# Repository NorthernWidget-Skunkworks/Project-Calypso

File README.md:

# Project-Calypso
The hardware and software designs for a turbidity measurement system, based on the work of a 2018 UMN senior design team

## Project Summary

Our team developed an open-source sensor to measure water turbidity. Turbidity, or "murkiness", increases when the water carries more sediment. Dissolved compounds can also increase turbidity by reducing water clarity. In general, less suspended and dissolved material makes better drinking water. Anyone may download and build this sensor (Design: https://doi.org/10.5281/zenodo.8177929).

*Two LEDs, red and infrared, send beams across the water to be measured, which lies within a transparent tube. These LED beams interact with the water, which reduces transmission and increases sidewas scatter. The detectors record both changes.*

The sensor, called "Project Calypso", shines lights from two LEDs through the water. These LEDs lie at right angles from each other along a clear square plastic tube. Detectors record the LEDs' brightness. The sensor directly across from each LED records light transmission. The sensor at 90 degrees from each LED records light scattering. Sediment in the water blocks the light and reduces transmission. Light can reflect off of sediment and scatter onto the sensor at 90 degrees. The scattering pattern depends on the wavelength of the light and sediment size. Therefore, we use both visible (red) and infrared light to learn about sediment size. Dissolved material reduces light transmission but does not scatter the light sideways. Because of this, Project Calypso can differentiate between sediment and dissolved compounds.

*CAD drawing of the LED and detector mount. Sensors and mount surround a transparent plastic tube with a square cross section. Water, along with any suspended and/or dissolved matter that it carries, fills this tube.*

*3-D printed LED and detctor mount, along with one of the installed custom circuit boards to hold the LEDs and light detectors.*

We characterized the Calypso sensor using standards of known turbidity. Sensor response varied systematically with water cloudiness and light wavelength. The Calypso turbidity-sensor system is not only an open-source alternative. It also provides more information than standard turbidity sensors.

*Increasing concentrations of Formaizin (left to right) cause the water to become systematically cloudier. We characterized the sensor using these standards.*

## Funding Support

Funding for this work came from the ***University of Minnesota Water Resources Center***, with support from the **USGS WRRI** program. This funding supported a grant to Wickert, Sandell, and Karwan, for their proposal entitled, *Open-Source Turbidity Sensor to Monitor Suspended and Dissolved Matter in Surface Water*.

<br/>
<br />This work is licensed under a <a rel="license" href="http://creativecommons.org/licenses/by-sa/4.0/">Creative Commons Attribution-ShareAlike 4.0 International License</a>.

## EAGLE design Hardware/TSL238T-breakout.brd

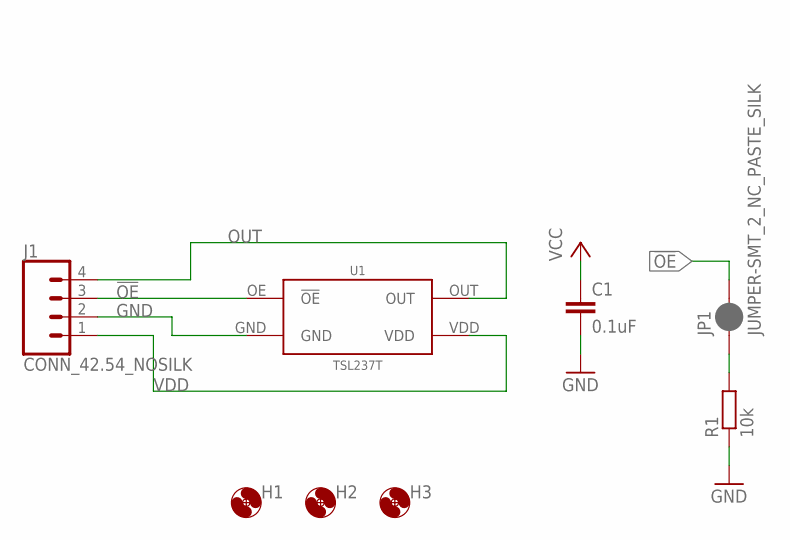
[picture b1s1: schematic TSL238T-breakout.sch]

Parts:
C1: 0.1uF; C0402
H1, H2, H3: MOUNTING_HOLE2_NP; 2_56
J1: CONN_42.54_NOSILK; 1X04_NOSILK
JP1: JUMPER-SMT_2_NC_PASTE_SILK; SMT-JUMPER_2_NC_PASTE_SILK
R1: 10k; R0402
U1: TSL237T

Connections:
!OE: J1.3, JP1.2, U1.OE (!OE)
GND: C1.2, J1.2, R1.1, U1.GND
unnamed: JP1.1, R1.2
OUT: J1.4, U1.OUT
VDD: C1.1, J1.1, U1.VDD

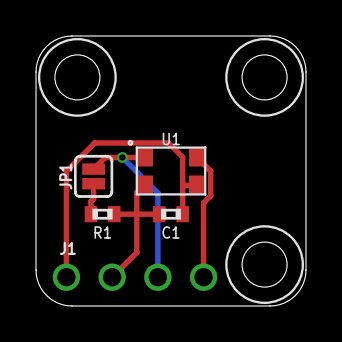
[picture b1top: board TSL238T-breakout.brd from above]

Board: 2 copper layers, 15.0 x 15.0 mm, 8 parts (0 on the bottom side), 5 nets.

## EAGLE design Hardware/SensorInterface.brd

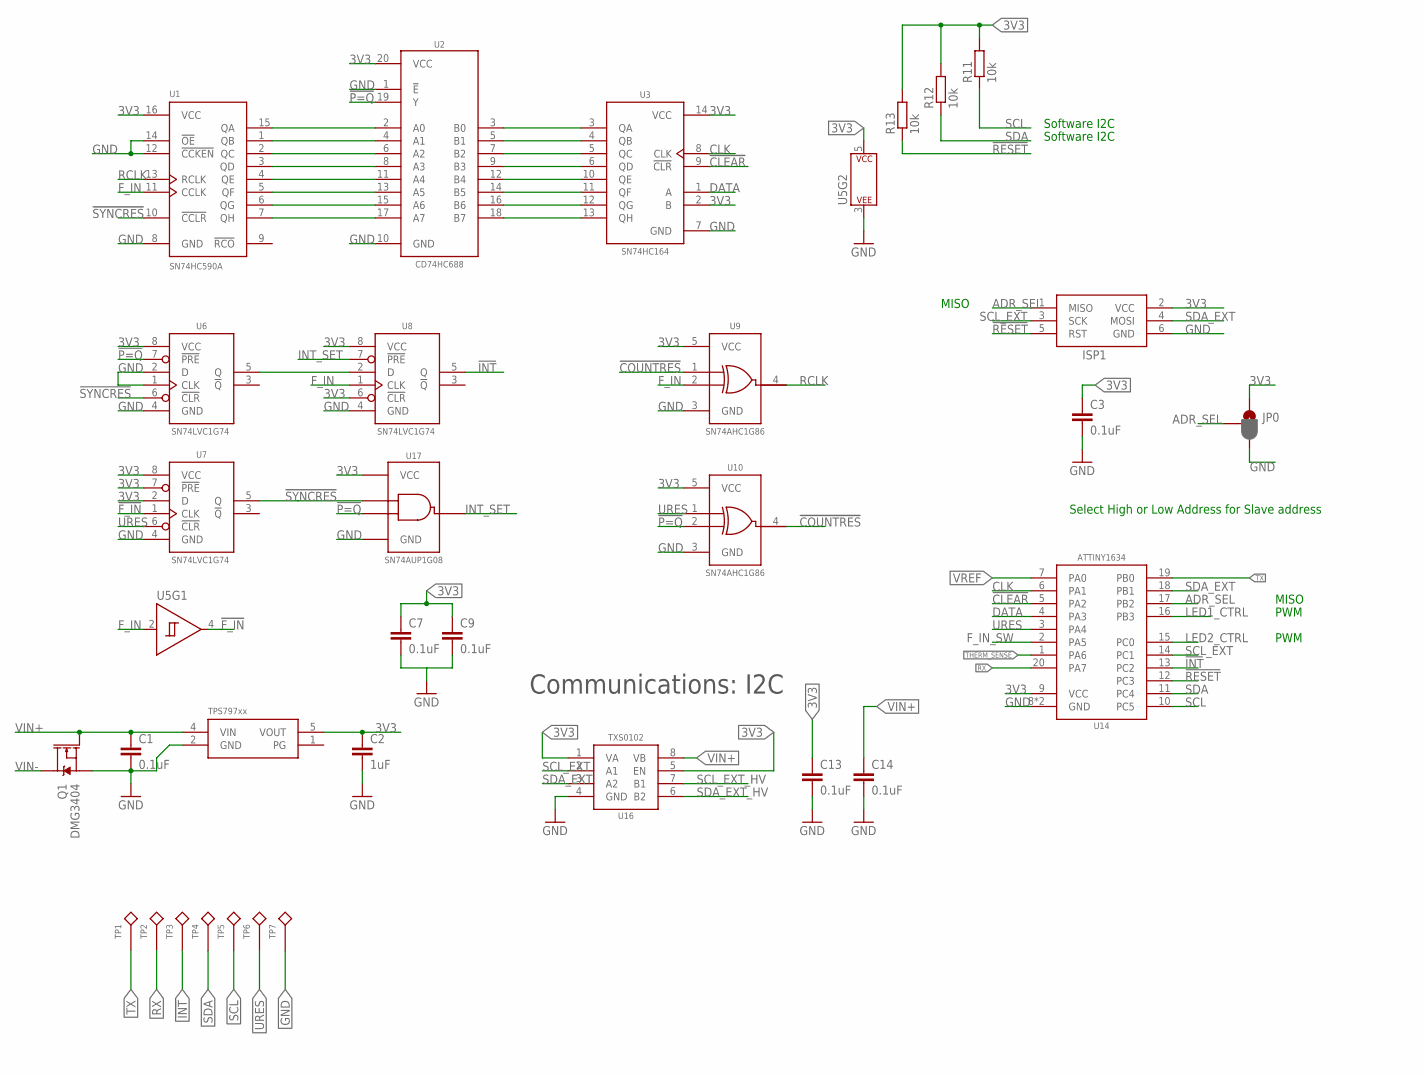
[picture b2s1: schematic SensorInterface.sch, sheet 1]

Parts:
C1, C7, C9: 0.1uF; C0603
C2: 1uF; C0603
C3, C13, C14: 0.1uF; C0402
ISP1: AVRISP-6; AVRISP
JP0: JUMPER-SMT_3_1-NC_PASTE_SILK; SMT-JUMPER_3_1-NC_PASTE_SILK
Q1: DMG3404; SOT23-3
R11, R12, R13: 10k; R0402
TP1, TP2, TP3, TP4, TP5, TP6, TP7: TESTPOINTRCU; TESTPOINT_0603
U1: SN74HC590AD; SO16
U2: CD74HCT688DW; SO-20DW
U3: SN74HC164D; SO14
U5: SN74LVC1G14DCK; DCK_R-PDSO-G5
U6, U7, U8: SN74LVC1G74DCU; DCU_(R-PDSO-G8)
U9, U10: SN74AHC1G86DCK; DCK_R-PDSO-G5
U14: ATTINY1634QFN; QFN20
U16: TXS0102DQM; DQM_R-PX2SON-N8
U17: SN74AUP1G08DCK; DCK_R-PDSO-G5
U$1: TPS79733; DCK_R-PDSO-G5

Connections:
3V3: C2.1, C3.1, C7.1, C9.1, C13.1, ISP1.2 (VCC), JP0.1, R11.2, R12.2, R13.2, U1.16 (VCC), U2.20 (VCC), U3.2 (B), U3.14 (VCC), U5.5 (P$V+), U6.8 (VCC), U7.2 (D), U7.7 (!PRE), U7.8 (VCC), U8.6 (!CLR), U8.8 (VCC), U9.5 (VCC), U10.5 (VCC), U14.9 (VCC), U16.1 (VA), U16.5 (EN), U17.5 (VCC), U$1.5 (VOUT); also elsewhere on the board
!CLEAR: U3.9 (!CLR), U14.5 (PA2)
!COUNTRES: U9.1 (A), U10.4 (Y)
!F_IN: U5.4 (Y), U7.1 (CLK)
!INT: TP3.1, U8.5 (Q), U14.13 (PC2)
!P=Q: U2.19 (Y), U6.7 (!PRE), U10.2 (B), U17.2 (B)
!RESET: ISP1.5 (RST), R13.1, U14.12 (PC3)
!SYNCRES: U1.10 (!CCLR), U6.6 (!CLR), U7.5 (Q), U17.1 (A)
ADR_SEL: ISP1.1 (MISO), JP0.2, U14.17 (PB2)
CLK: U3.8 (CLK), U14.6 (PA1)
DATA: U3.1 (A), U14.4 (PA3)
F_IN: U1.11 (CCLK), U5.2 (A), U8.1 (CLK), U9.2 (B); also elsewhere on the board
F_IN_SW: U14.2 (PA5); also elsewhere on the board
GND: C1.2, C2.2, C3.2, C7.2, C9.2, C13.2, C14.2, ISP1.6 (GND), JP0.3, Q1.2 (S), TP7.1, U1.8 (GND), U1.12 (!CCKEN), U1.14 (!OE), U2.1 (!E), U2.10 (GND), U3.7 (GND), U5.3 (P$V-), U6.1 (CLK), U6.2 (D), U6.4 (GND), U7.4 (GND), U8.4 (GND), U9.3 (GND), U10.3 (GND), U14.8 (GND), U14.EP (GND), U16.4 (GND), U17.3 (GND), U$1.2 (GND); also elsewhere on the board
INT_SET: U8.7 (!PRE), U17.4 (Y)
LED1_CTRL: U14.16 (PB3); also elsewhere on the board
LED2_CTRL: U14.15 (PC0); also elsewhere on the board
unnamed: U1.15 (QA), U2.2 (A0)
unnamed: U1.1 (QB), U2.4 (A1)
unnamed: U1.2 (QC), U2.6 (A2)
unnamed: U1.3 (QD), U2.8 (A3)
unnamed: U1.4 (QE), U2.11 (A4)
unnamed: U1.5 (QF), U2.13 (A5)
unnamed: U1.6 (QG), U2.15 (A6)
unnamed: U1.7 (QH), U2.17 (A7)
unnamed: U2.3 (B0), U3.3 (QA)
unnamed: U2.5 (B1), U3.4 (QB)
unnamed: U2.7 (B2), U3.5 (QC)
unnamed: U2.9 (B3), U3.6 (QD)
unnamed: U2.12 (B4), U3.10 (QE)
unnamed: U2.14 (B5), U3.11 (QF)
unnamed: U2.16 (B6), U3.12 (QG)
unnamed: U2.18 (B7), U3.13 (QH)
unnamed: U6.5 (Q), U8.2 (D)
RCLK: U1.13 (RCLK), U9.4 (Y)
RX: TP2.1, U14.20 (PA7)
SCL: R11.1, TP5.1, U14.10 (PC5); also elsewhere on the board
SCL_EXT: ISP1.3 (SCK), U14.14 (PC1), U16.2 (A1)
SCL_EXT_HV: U16.7 (B1); also elsewhere on the board
SDA: R12.1, TP4.1, U14.11 (PC4); also elsewhere on the board
SDA_EXT: ISP1.4 (MOSI), U14.18 (PB1), U16.3 (A2)
SDA_EXT_HV: U16.6 (B2); also elsewhere on the board
THERM_SENSE: U14.1 (PA6); also elsewhere on the board
TX: TP1.1, U14.19 (PB0)
URES: TP6.1, U7.6 (!CLR), U10.1 (A), U14.3 (PA4)
VIN+: C1.1, C14.1, Q1.1 (G), U16.8 (VB), U$1.4 (VIN); also elsewhere on the board
VIN-: Q1.3 (D); also elsewhere on the board
VREF: U14.7 (PA0); also elsewhere on the board

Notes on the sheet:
Software I2C
Select High or Low Address for Slave address
Communications: I2C
PWM
MISO

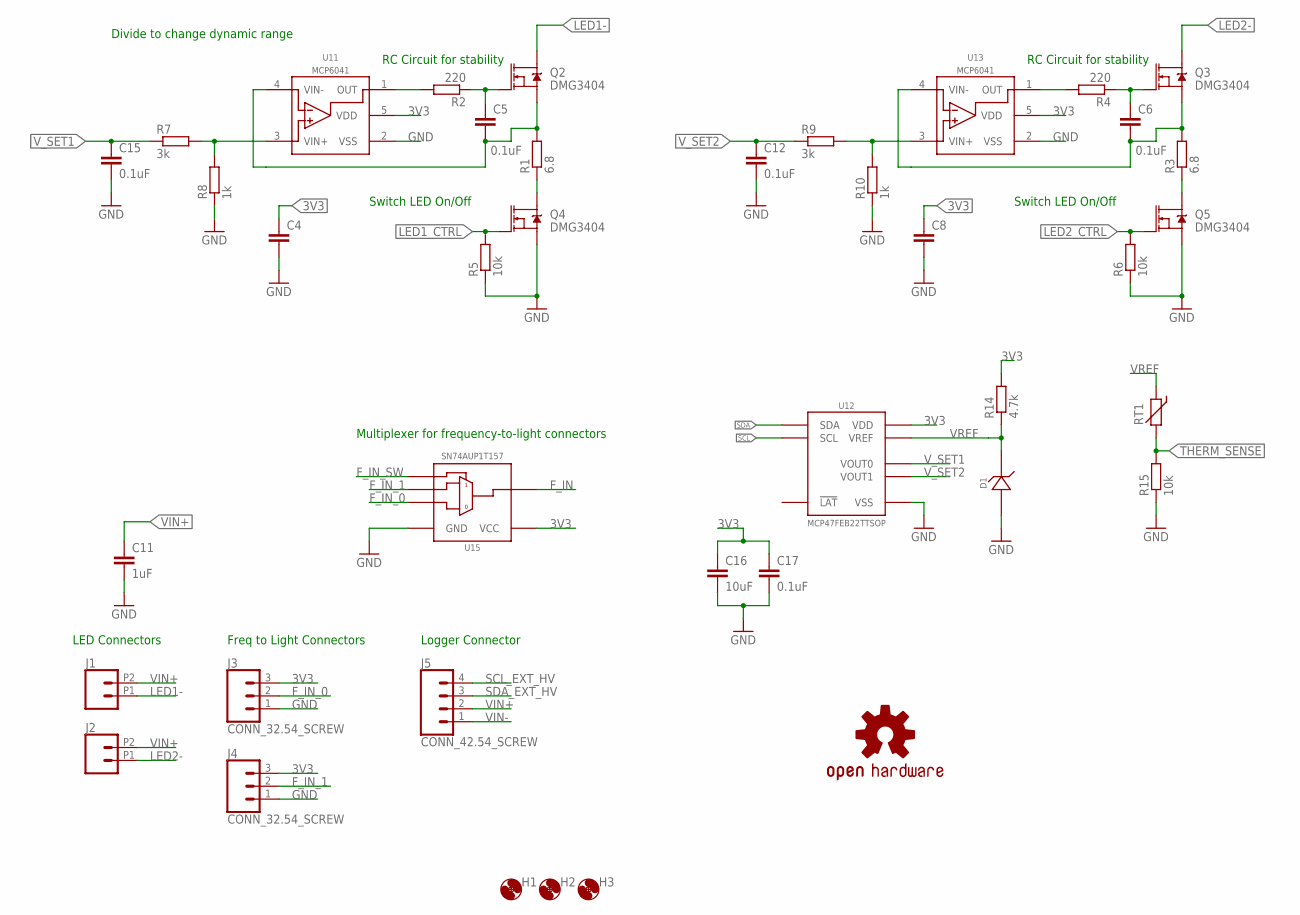
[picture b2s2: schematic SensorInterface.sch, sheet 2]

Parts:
C4, C8: C-EU0.1UFC0402; C0402
C5, C6, C12, C15, C17: 0.1uF; C0603
C11: 1uF; C0603
C16: 10uF; C0805
D1: LM40402.048; SOT23-3
H1, H2, H3: MOUNTING_HOLE2_NP; 2_56
J1, J2: CONN_02SCREW_2.54; 1X02_2.54_SCREWTERM
J3, J4: CONN_32.54_SCREW; 1X03_SCREW
J5: CONN_42.54_SCREW; 1X04_SCREW
LOGO1: OSHW-LOGOM; OSHW-LOGO-M
Q2, Q3, Q4, Q5: DMG3404; SOT23-3
R1, R3: 6.8; R0603
R2, R4: 220; R0603
R5, R6, R15: 10k; R0603
R7, R9: 3k; R0603
R8, R10: 1k; R0603
R14: 4.7k; R0603
RT1: THERMISTOR10K; R0603
U11, U13: MCP6041; SOT23-5
U12: MCP47FEB22TTSOP; TTSOP_8
U15: SN74AUP1T157DCK; DCK_R-PDSO-G6

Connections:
3V3: C4.1, C8.1, C16.1, C17.1, J3.3, J4.3, R14.2, U11.5 (VDD), U12.1 (VDD), U13.5 (VDD), U15.5 (VCC); also elsewhere on the board
F_IN: U15.6 (Y); also elsewhere on the board
F_IN_0: J3.2, U15.3 (B)
F_IN_1: J4.2, U15.1 (A)
F_IN_SW: U15.4 (C); also elsewhere on the board
GND: C4.2, C8.2, C11.2, C12.2, C15.2, C16.2, C17.2, D1.2 (A), J3.1, J4.1, Q4.2 (S), Q5.2 (S), R5.1, R6.1, R8.1, R10.1, R15.1, U11.2 (VSS), U12.5 (VSS), U13.2 (VSS), U15.2 (GND); also elsewhere on the board
LED1-: J1.P1 (1), Q2.3 (D)
LED1_CTRL: Q4.1 (G), R5.2; also elsewhere on the board
LED2-: J2.P1 (1), Q3.3 (D)
LED2_CTRL: Q5.1 (G), R6.2; also elsewhere on the board
unnamed: R7.2, R8.2, U11.3 (VIN+)
unnamed: C6.2, Q3.2 (S), R3.2, U13.4 (VIN-)
unnamed: C6.1, Q3.1 (G), R4.1
unnamed: C5.2, Q2.2 (S), R1.2, U11.4 (VIN-)
unnamed: C5.1, Q2.1 (G), R2.1
unnamed: R2.2, U11.1 (OUT)
unnamed: R4.2, U13.1 (OUT)
unnamed: Q5.3 (D), R3.1
unnamed: Q4.3 (D), R1.1
unnamed: R9.2, R10.2, U13.3 (VIN+)
SCL: U12.7 (SCL); also elsewhere on the board
SCL_EXT_HV: J5.4; also elsewhere on the board
SDA: U12.8 (SDA); also elsewhere on the board
SDA_EXT_HV: J5.3; also elsewhere on the board
THERM_SENSE: R15.2, RT1.2 (1); also elsewhere on the board
VIN+: C11.1, J1.P2 (2), J2.P2 (2), J5.2; also elsewhere on the board
VIN-: J5.1; also elsewhere on the board
VREF: D1.1 (C), R14.1, RT1.1 (2), U12.2 (VREF); also elsewhere on the board
V_SET1: C15.1, R7.1, U12.3 (VOUT0)
V_SET2: C12.1, R9.1, U12.4 (VOUT1)

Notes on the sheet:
RC Circuit for stability
LED Connectors
Freq to Light Connectors
Logger Connector
Switch LED On/Off
Divide to change dynamic range
Multiplexer for frequency-to-light connectors

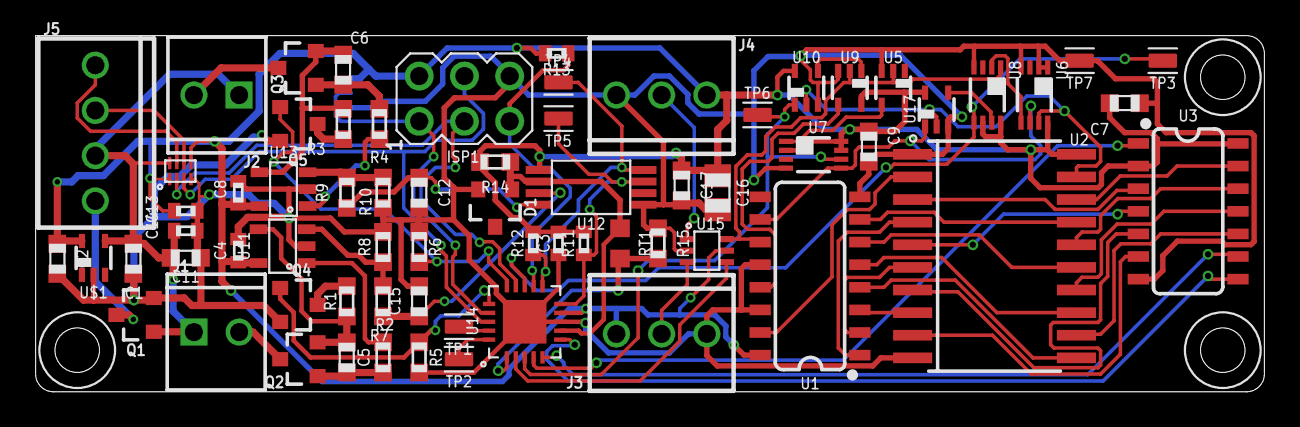
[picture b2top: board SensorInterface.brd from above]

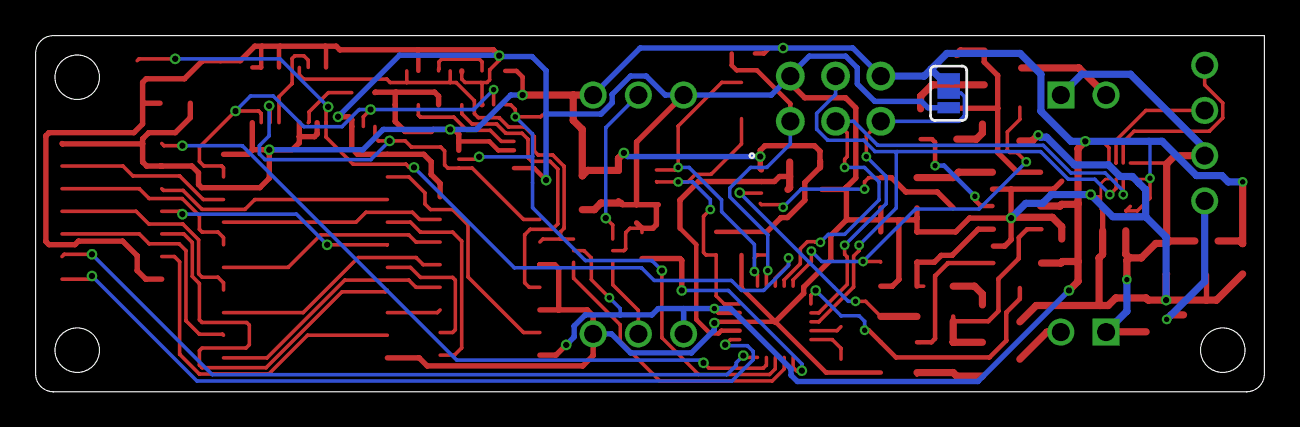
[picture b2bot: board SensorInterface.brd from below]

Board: 2 copper layers, 69.0 x 20.0 mm, 73 parts (2 on the bottom side), 64 nets.

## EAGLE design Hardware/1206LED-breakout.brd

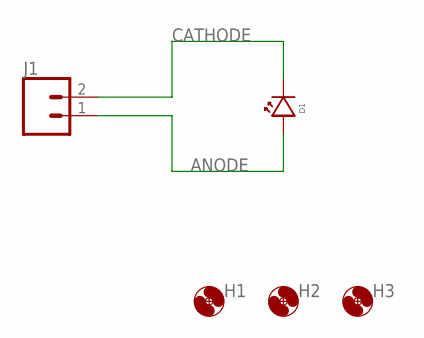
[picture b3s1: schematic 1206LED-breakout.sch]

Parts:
D1: LED1206; LED_1206
H1, H2, H3: MOUNTING_HOLE2_NP; 2_56
J1: CONN_021X02_NO_SILK; 1X02_NO_SILK

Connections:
ANODE: D1.ANODE, J1.1
CATHODE: D1.CATHODE, J1.2

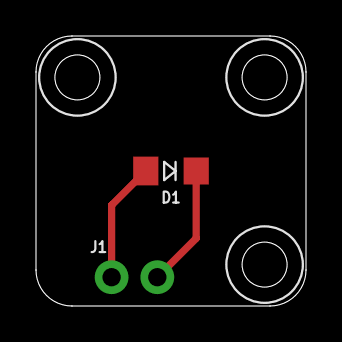
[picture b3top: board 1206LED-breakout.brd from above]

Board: 2 copper layers, 15.0 x 15.0 mm, 5 parts (0 on the bottom side), 2 nets.

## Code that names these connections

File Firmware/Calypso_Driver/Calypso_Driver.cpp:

#define LED1 0  //Define values of LEDs for side indication
#define LED2 1

#define URES 4 //uReset on D4
#define LED1_CTRL 14 //LED 1 control pin on D14
#define LED2_CTRL 13 //LED 2 control pin on D13
#define DATA 5 //Data line to counter on D5
#define CLK 7 //Clock line to counter of D0
#define CLEAR 6 //Clear line to counter on D7
#define DONE 11 //Int line to comparator on D1 //FIX! Change name to INT??
#define F_IN_SW 3 //Input switch on D3
#define THERM_PIN A3 //Thermistor input on ADC3
#define SDA_SOFT PIN_C4
#define SCL_SOFT PIN_C5


#define ADR_SEL_PIN 15 //Digital pin 15 is used to test which device address should be used

uint16_t Res = 6800; //Resistance in mOhms of load resistor(s)
uint8_t Div = 4; //Division factor

uint8_t Config = 0; //Global config value

uint8_t Reg[22] = {0}; //Initialize registers

SlowSoftI2CMaster si = SlowSoftI2CMaster(SDA_SOFT, SCL_SOFT, true);  //Initialize software I2C  //FIX! Check pin values!

//FIX! Update values!
volatile uint8_t ADR = 0x40; //Use arbitraty address, change using generall call??
const uint8_t ADR_Alt = 0x41; //Alternative device address  //WARNING! When a #define is used instead, problems are caused

volatile bool StopFlag = false; //Used to indicate a stop condition 
volatile uint8_t RegID = 0; //Used to denote which register will be read from
volatile bool RepeatedStart = false; //Used to show if the start was repeated or not

void setup() {
	Reg[CTRL] = 0x00; //Set Config to POR value
	// pinMode(9, OUTPUT);
	pinMode(10, OUTPUT);
	// digitalWrite(9, HIGH);
	digitalWrite(10, HIGH); //Turn on LED switches 

	pinMode(LED1_CTRL, OUTPUT);
	pinMode(DATA, OUTPUT);
	pinMode(CLK, OUTPUT);
	pinMode(CLEAR, OUTPUT);
	pinMode(URES, OUTPUT);
	pinMode(DONE, INPUT);
	if(!digitalRead(ADR_SEL_PIN)) ADR = ADR_Alt; //If solder jumper is bridged, use alternate address //DEBUG!
  	Wire.begin(ADR);  //Begin slave I2C

  	Wire.onAddrReceive(addressEvent); // register event
	Wire.onRequest(requestEvent);     // register event
	Wire.onReceive(receiveEvent);
	Wire.onStop(stopEvent);

	si.i2c_init(); //Begin I2C master
}

void loop() {
	if(StartSample == true) {
		//Add sample procedure!
		//Set LEDs
		//Set Counter
		//Clear counter
		//Start timer
		//release counter
	}
	delay(100); //FIX! Keep?
}

//Current given in uA
int SetCurrent(long Current, bool Side) //Set current drive for led, use Side to set which LED to set, 0 for LED1, 1 for LED2
{
	//ADD VOLTAGE DIVIDER VALUE!!??
	//RETURN BAD VALUE IF SET OUTSIDE OF RANGE!??
	uint16_t Voltage = ((Current*Res)/500)*Div; //Determine current set from load resistor 500 = 4096/2048000, bits/uV range
	Wire.beginTransmission(DAC_Adr[Side]);  //FIX! Update for new DAC!
	Wire.write(MCP4726_CMD_WRITEDAC);
	Wire.write(Voltage / 16);                   // Upper data bits          (D11.D10.D9.D8.D7.D6.D5.D4)
	Wire.write((Voltage % 16) << 4);            // Lower data bits          (D3.D2.D1.D0.x.x.x.x)
	Wire.endTransmission();
}

//Set bit value
int SetVoltageRaw(uint16_t Val, bool Side) 
{
	//ADD VOLTAGE DIVIDER VALUE!!??
	//RETURN BAD VALUE IF SET OUTSIDE OF RANGE!??
	// uint16_t Voltage = ((Current*Res)/806)*Div; //Determine current set from load resistor 806 = 4096/3300000, bits/uV range
	Wire.beginTransmission(DAC_Adr[Side]); //FIX! Update for new DAC!
	Wire.write(MCP4726_CMD_WRITEDAC);
	Wire.write(Val / 16);                   // Upper data bits          (D11.D10.D9.D8.D7.D6.D5.D4)
	Wire.write((Val % 16) << 4);            // Lower data bits          (D3.D2.D1.D0.x.x.x.x)
	Wire.endTransmission();
}

void SetCount(uint8_t Val)
{
	bool Dummy = false; 
	DDRB = DDRB | 0x01; //Set pin PB0 as output  //DEBUG!
	DDRA = DDRA | 0x28; //Set pin PA5 and pin PA3 as output  //DEBUG!
	PORTA = PORTA | 0x08; //Turn Clear Off
	PORTA = PORTA & 0xDF; //Clear PA5 
	// Val = Val << 0x05; //Offset to allign with PORTA
	for(int i = 7; i >= 0; i--) {
		//FAST MODE
		PORTB = PORTB & 0xFE; //Clear bit, drive clock low  //DEBUG!
		asm("nop \n"); //pause for one clock cycle
//		 PORTA = PORTA | ((Val >> i) & 0x01 ) << 0x05;  //DEBUG!
    PORTA = PORTA & 0xDF;
		PORTA = PORTA | (Val >> 0x02) & 0x20;  //DEBUG!
		//// PORTA = PORTA | (Val  << (0x05 + i)) & 0x20;  //DEBUG!
		asm("nop \n"); //pause for one clock cycle
		PORTB = PORTB | 0x01; //Set bit, drive clock high  //DEBUG!
		asm("nop \n"); //pause for one clock cycle
		Val = Val << 0x01; //Shift to new val


//		 digitalWrite(CLK, LOW); //Set clock low
//		 digitalWrite(DATA, (Val >> i) & 0x01); //Write LSB to DATA pin
//		 digitalWrite(CLK, HIGH); //Clock values in on rising edge
	}
}

void ClearCount()
{
	digitalWrite(CLEAR, LOW);
	delayMicroseconds(1);
	// delay(1); //Wait for clear to take place
	digitalWrite(CLEAR, HIGH); //Return to nominal value
}

void SplitAndLoad(uint8_t Pos, unsigned int Val) //Write 16 bits
{
	uint8_t Len = sizeof(Val);
	for(int i = Pos; i < Pos + Len; i++) {
		Reg[i] = (Val >> (i - Pos)*8) & 0xFF; //Pullout the next byte
	}
}

void SplitAndLoad(uint8_t Pos, long Val)  //Write 32 bits  //FIX! Needed?
{
	uint8_t Len = sizeof(Val);
	for(int i = Pos; i < Pos + Len; i++) {
		Reg[i] = (Val >> (i - Pos)*8) & 0xFF; //Pullout the next byte
	}
}

boolean addressEvent(uint16_t address, uint8_t count)
{
	RepeatedStart = (count > 0 ? true : false);
	return true; // send ACK to master
}

void requestEvent()
{	
	//Allow for repeated start condition 
	if(RepeatedStart) {  //FIX! Make repeated start actually work!
		for(int i = 0; i < 2; i++) {
			Wire.write(Reg[RegID + i]);
		}
	}
	else {
		Wire.write(Reg[RegID]);
	}
}

void receiveEvent(int DataLen) 
{
    //Write data to appropriate location
    if(DataLen == 2){
	    //Remove while loop?? 
	    while(Wire.available() < 2); //Only option for writing would be register address, and single 8 bit value
	    uint8_t Pos = Wire.read();
	    uint8_t Val = Wire.read();
	    //Check for validity of write??
	    Reg[Pos] = Val; //Set register value
	}

	if(DataLen == 1){
		RegID = Wire.read(); //Read in the register ID to be used for subsequent read
	}
}

void stopEvent() 
{
	StopFlag = true;
	//End comunication
}

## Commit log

2018-05-16 Added LED current drive simulations
2018-05-29 Initial Schematic Layout, Edits to simulation
    Initial schematic layout complete, needs verification, made edits to the simulator on the LED current drive to both simulate the RC compensator network and the input voltage division
2018-05-31 Updated frame info
2018-10-15 Cleanup and added documentation (design drawings)
2018-12-17 Edits to schematic and simulations
2018-12-18 Eagle files in same directory
2018-12-18 +1 detector, MUX, 3V3 labels
2018-12-18 LED system laid out (mostly)
2018-12-18 Initial routing complete with DRC
2018-12-18 CC-BY-SA
2018-12-24 Silkscreen for initial prototype
2018-12-24 Pin labels
2019-01-02 Post-review update * Shortened analog feedback and power traces * Checked trace widths for uniformity and appropriateness * Added 5V/3.3V level conversion * Pull-ups on I2C (internal) and RESET
2019-01-02 Board cleanup
    Cleaned up layout, increased silkscreen width, increased power path width, changed layout of 3v3 reg
2019-01-04 Actual board cleanup
    Fixed empty push issue, see last commit
2019-01-04 Schulz to board attribution
2019-01-04 thicker power path traces
2019-01-04 Added gerbers, minor cleanup, v0.0.0 submitted to fab
    Cleaned up board and made some minor changes to decoupling capacitor layout, adjusted some traces. Generated gerbers and submitted boards for v0.0
2019-01-16 Move and define caps
2019-01-16 Trace updates for caps
2019-01-19 Added basic firmware test file to help with development
2019-01-19 first draft
2019-01-19 Labels, 3rd hole
2019-01-19 re-center detector
2019-01-19 rm unnecessary label
2019-01-19 LED, also 15mm square
2019-01-24 Added SetCount and ClearCount
    Added functions for setting and clearing quantity set shift register. Increased speed with port manipulation. Still optimization to be done
2019-01-25 Continued testing and speed improvements to register loading
    Significantly improved speed of loading comparison register, other continued testing
2019-01-29 Fixed clock in function in test firmware
    There was an error in the serial clocking function in the firmware (neglected to clear a bit in the register), error has been fixed
2019-01-30 Updated breakouts and main board, schematic v0.1 updates
    Updated schematic for main unit to v0.1, incorporating updates from testing of v0.0 unit
    Minor updates to breakout boards, adding passives and updating components
2019-01-31 Routed; DRC passed
2019-02-01 Reroute initial stage
2019-02-02 Continued layout update
    Layout is functional for v0.1, review and clean up still required but functional layout completed
2019-02-04 Mounting hole in NE corner
2019-02-04 Added mount holes, cleaned up sim
    Cleaned up simulation files and gitignore, added mounting holes to board
2019-02-04 Layout cleanup ready for review
2019-02-04 SE corner hole added
2019-02-06 Minor cleanup, generated gerbers
    Cleaned up silkscreen on board and generated gerbers for main board and breakouts
2019-02-07 Added PDFs and replaced OSHW logo
    Added PDFs for board (clean) and schematic (nearly clean), also replaced the OSHW logo with one from ColdSilicon which uses the correct layer
2019-02-13 Added preliminary driver interface
    Added in progress Calypso firmware driver, also added additional labeling to schematic for sensor interface
2019-02-19 Continued firmware dev and testing
    Tested current control over I2C, tested counting and count setting, system able to return pulse time values over I2C
2019-02-19 Fix edge trigger and overflow
    Fixed interrupt in firmware so it only updates data values on rising edges, also changed data type in demo software to prevent overflow of time values
2019-02-20 Added serial interface to Calypso demo
    Added serial backbone to Calypso demo, minor fixes/updates to Driver, added header to all. Added beginning of register map, still needs to be fully populated
2019-02-21 Improved serial interface, added basic sweep function
    Several improvements and bug fixes to the serial interface, still need to deal with the lockup issue on the firmware side. Also added dimensional documentation to the TSL238T breakout
2019-02-27 Cleaned up schematic for report
2019-03-01 Updates to frimware and demo software
    Support for raw output setting, and gain and mode adjustment added
2020-05-01 rm cruft
2020-05-01 stencil mount and optics mount
2020-05-01 GNU GPL v3 for code products (software, firmware, etc.)
2023-07-25 Assembly instructions: Senior Design Prototype (2018)
2023-07-25 Senior Design 2018 archive Design files from the working metal-box prototype Here, included to document this design phase
2023-07-25 Bill of materials
2023-07-26 Senior-design launch docs
2023-07-26 Raw code from Senior Design project
2023-07-26 Formazin standard, varying concentration.
2023-07-26 Move old Hardware into Sr Design folder.
2023-07-26 Temporary lock files
2023-07-26 Add UMN WRC logo for acknowledgement.
2023-07-26 UMN WRC funding acknowledgement
2023-07-26 Citation: PIs, Bobby, Design Team
2023-07-26 Sr. Design Fig
2023-07-26 Add summary (first part) and LED+detector fig.
2023-07-26 Clarify LED-beam figure caption.
2023-07-26 Add simple description of how Calypso works.
2023-07-26 2x "at".
2023-07-26 Use Hemingway simplification of first Summary paragraph.
2023-07-26 LED mount
2023-07-26 CAD sensor and mount.
2023-07-26 Photo of the 3-D printed mount and custom PCB.
2023-07-26 Turbidity standards.
2023-07-26 Sensor characterization using Formazin standards.
2023-07-26 Increment version: v0.3.0.

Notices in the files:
parts and their libraries:
bschulz: This work is licensed under the Creative Commons Attribution-ShareAlike 4.0
SparkFun-Jumpers: Licensing: Creative Commons ShareAlike 4.0 International - https://creativecommons.org/licenses/by-sa/4.0
